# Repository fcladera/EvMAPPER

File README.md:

# EvMAPPER

This is the source code repository for EvMAPPER, a high altitude orthomapping
framework.

## Repository overview
 - `CAD`: CAD models to attach the sensor stack (EV + RGB + VN100 + range sensor) to the Falcon 4 UAV. 
 - `PCB`: PCB for time synchronization.
 - `ha_python_utils`: Python utilities for high altitude data processing.
 - `Notebooks`: Jupyter notebooks for data processing and visualization.

You can access our preprint on [arXiv](https://arxiv.org/abs/2409.18120),
and our [video presentation](https://www.youtube.com/watch?v=8mgCMnaMDdM).

## Citation
```
@article{cladera2024evmapper,
  title={EvMAPPER: High Altitude Orthomapping with Event Cameras},
  author={Cladera, Fernando and Chaney, Kenneth and Hsieh, M Ani and Taylor, Camillo J and Kumar, Vijay},
  journal={arXiv preprint arXiv:2409.18120},
  year={2024}
}
```

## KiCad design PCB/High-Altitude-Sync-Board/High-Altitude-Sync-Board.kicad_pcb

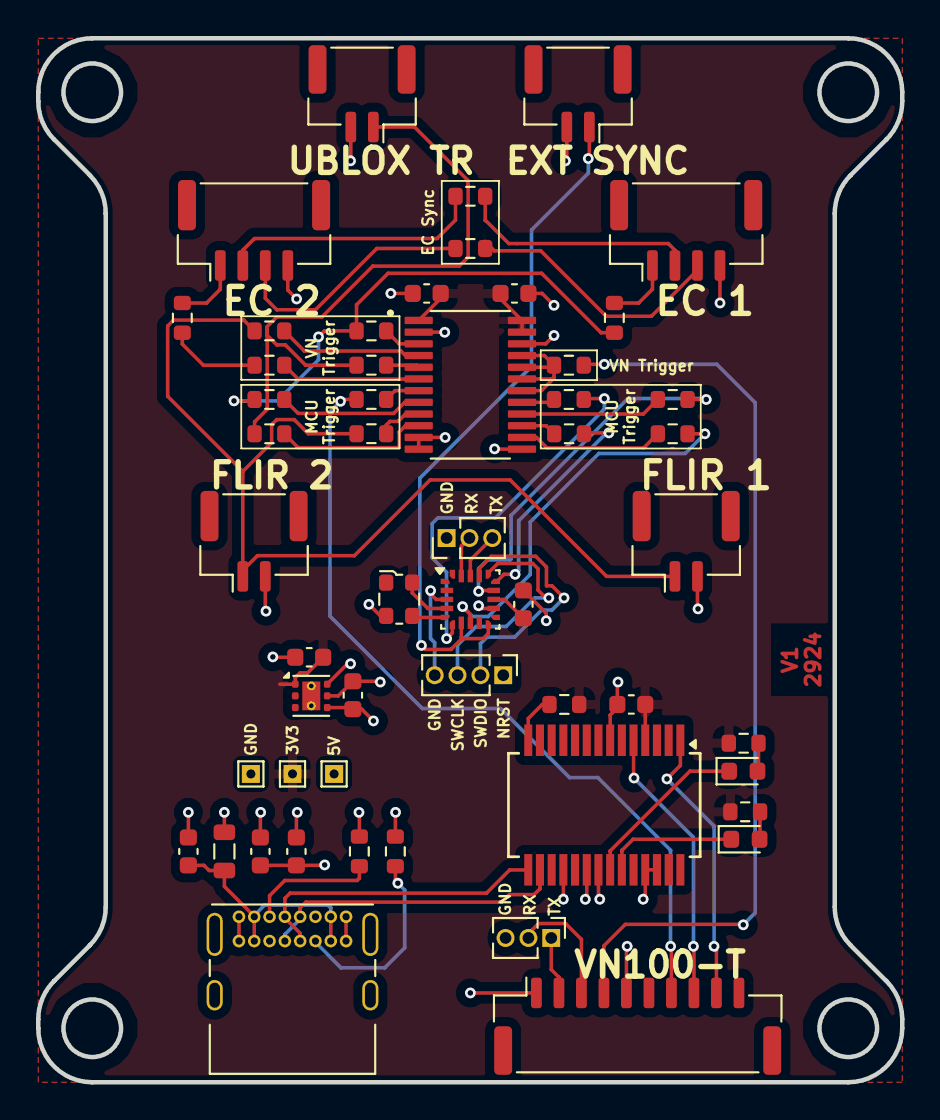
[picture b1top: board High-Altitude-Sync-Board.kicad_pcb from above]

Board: 4 copper layers, 48.0 x 58.0 mm, 53 parts (0 on the bottom side), 53 nets.

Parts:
C1, C2, C3, C5, C7: 100nF; C_0603_1608Metric
C4: 10nF_X7R; C_0603_1608Metric
C6, C9, C10: 4.7uF; C_0603_1608Metric
D1, D2: LED; LED_0603_1608Metric
J1: USB_C_Receptacle_USB2.0_14P; USB_C_Receptacle_GCT_USB4085
J2, J20: SM02B-GHS-TB; JST_GH_SM02B-GHS-TB_1x02-1MP_P1.25mm_Horizontal
J7: VN100_T_CONN; JST_GH_SM10B-GHS-TB_1x10-1MP_P1.25mm_Horizontal
J17: VN100T-UPDATE; PinHeader_1x03_P1.27mm_Vertical
J18, J19: BM02B-GHS-TBT; JST_GH_BM02B-GHS-TBT_1x02-1MP_P1.25mm_Vertical
J23, J25: BM04B-GHS-TBT; JST_GH_BM04B-GHS-TBT_1x04-1MP_P1.25mm_Vertical
J24: SWD; PinHeader_1x04_P1.27mm_Vertical
J26: UART; PinHeader_1x03_P1.27mm_Vertical
L1: MI0805K400R-10; L_0805_2012Metric
R1, R2: 5.1k; R_0603_1608Metric
R3, R4, R5, R6, R7, R8, R9, R11, R12, R13, R14, R15, R16, R19, R20, R21, R22: 0R; R_0603_1608Metric
R10, R17: 1k1; R_0603_1608Metric
R18: 10k; R_0603_1608Metric
TP1: 5V TP; TestPoint_THTPad_1.0x1.0mm_Drill0.5mm
TP2: GND TP; TestPoint_THTPad_1.0x1.0mm_Drill0.5mm
TP3: 3V3 TP; TestPoint_THTPad_1.0x1.0mm_Drill0.5mm
U1: SN74AXC8T245PWR; SOP65P640X120-24N
U2: FT232RL; SSOP-28_5.3x10.2mm_P0.65mm
U3: LP5912-3.3DRV; WSON-6-1EP_2x2mm_P0.65mm_EP1x1.6mm_ThermalVias
U4: STM32L011F3Ux; ST_UFQFPN-20_3x3mm_P0.5mm
X1: ECS-2520MV; Oscillator_SMD_ECS_2520MV-xxx-xx-4Pin_2.5x2.0mm

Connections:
+3V3: C1.1, C2.1, C3.1, C7.1, C10.1, R10.1, R17.1, R18.1, TP3.1, U1.1 (VCCA), U1.23 (VCCB), U1.24 (VCCB), U2.4 (VCCIO), U3.1 (OUT), U4.4 (VDDA), U4.13 (VDD), X1.4 (VDD)
+5V: C5.1, C6.1, C9.1, J7.1, L1.1, TP1.1, U2.20 (VCC), U3.4 (EN), U3.6 (IN)
/EC_1_TRIGGER_IN: R3.1, R11.1, R22.1
/EC_2_TRIGGER_IN: R7.1, R19.1
/EXT_SYNC: J20.1, U4.7 (PA4), U4.10 (PA7)
/FLIR_TRIGGER_IN: J18.1, J19.1, R5.1, R13.1
/HSE: U4.5 (PA0), X1.3 (OUT)
/NRST: J24.4, U4.3 (NRST)
/SWCLK: J24.2, U4.17 (PA14)
/SWDIO: J24.3, U4.16 (PA13)
/SYNC_IN_N4: J23.3, R21.2
/SYNC_IN_P3: J23.2, R20.2
/SYNC_OUT_N2: J25.3, R21.1
/SYNC_OUT_P1: J25.2, R20.1
/TIM2_CH1: R16.2, U4.8 (PA5)
/TIM2_CH2: R9.2, U4.6 (PA1)
/TIM21_CH1: R14.2, U4.15 (PA10)
/TIM21_CH2: R12.2, U4.14 (PA9)
/UBLOX_TRIGGER_IN: J2.1, R6.1, R15.1
/VN-100T-RX1: J7.3, J17.2
/VN-100T-RX2_TTL: J7.9, U2.1 (TXD)
/VN-100T-SYNC-IN: J7.7, R8.1
/VN-100T-SYNC-OUT: J7.4, R4.2
/VN-100T-TX1: J7.2, J17.1
/VN-100T-TX2_TTL: J7.8, U2.5 (RXD)
GND: C1.2, C2.2, C3.2, C4.2, C5.2, C6.2, C7.2, C9.2, C10.2, J1.A1 (GND), J1.A12 (GND), J1.B1 (GND), J1.B12 (GND), J2.2, J7.5, J17.3, J18.2, J19.2, J20.2, J23.4, J24.1, J25.4, J26.1, R1.1, R2.1, TP2.1, U1.2 (DIR1), U1.11 (DIR2), U1.12 (GND), U1.13 (GND), U1.22 (~OE), U2.7 (GND), U2.18 (GND), U2.21 (GND), U2.25 (AGND), U2.26 (TEST), U3.5 (GND), U3.7 (EP), U4.12 (VSS), X1.2 (GND)
unnamed: C4.1, J1.A4 (VBUS), J1.A9 (VBUS), J1.B4 (VBUS), J1.B9 (VBUS), L1.2
unnamed: D1.2 (A), R10.2
unnamed: D1.1 (K), U2.23 (CBUS0)
unnamed: D2.2 (A), R17.2
unnamed: D2.1 (K), U2.22 (CBUS1)
unnamed: J1.A5 (CC1), R1.2
unnamed: J1.B5 (CC2), R2.2
unnamed: J23.1, R19.2
unnamed: J25.1, R22.2
unnamed: J26.2, U4.19 (PB7)
unnamed: J26.3, U4.18 (PB6)
unnamed: R3.2, U1.3 (A1)
unnamed: R5.2, U1.4 (A2)
unnamed: R6.2, U1.5 (A3)
unnamed: R7.2, U1.6 (A4)
unnamed: R8.2, U1.7 (A5)
unnamed: R11.2, U1.8 (A6)
unnamed: R13.2, U1.9 (A7)
unnamed: R15.2, U1.10 (A8)
unnamed: R4.1, U1.18 (B4), U1.19 (B3), U1.20 (B2), U1.21 (B1)
unnamed: R9.1, U1.17 (B5)
unnamed: R12.1, U1.16 (B6)
unnamed: R14.1, U1.15 (B7)
unnamed: R16.1, U1.14 (B8)
unnamed: R18.2, U2.14 (CBUS3)
unnamed: J1.A6 (D+), J1.B6 (D+), U2.15 (USBD+)
unnamed: J1.A7 (D-), J1.B7 (D-), U2.16 (USBD-)

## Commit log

2024-07-10 First version of the hardware CAD
2024-07-12 Setup Board for PCB
2024-07-12 Removed prl file and moved PCB outline into right folder
2024-07-12 Add .gitignore for PCB dir
2024-07-15 First draft of High Altitude sync board with outline
2024-07-15 Updated .gitignore for PCB
2024-07-15 Routed RS232
2024-07-15 Routed top part of the sync board
2024-07-16 Almost final routing of High Altitude Sync Board
2024-07-17 High Altitude Sync Board - V1
2024-07-17 Updated CAD with PCB and LM5JCM lens
2024-07-17 Ignore step files and pngs in CAD
2024-07-20 Add MountingBlock to mount to Falcon 4. Fix small defects in other parts.
2024-08-01 Reduced the size of the CameraMount plate, with newer MountingBlocks
2024-08-06 Poetry pyproject.toml file
2024-08-06 Notebook to analyze IMU clock and triggers
2024-08-13 Time synchronization tests for all high frequency sensors
2024-08-20 Time synchronization notebook for all sensors
2024-08-20 Renamed time synchronization notebook
2024-08-20 Simple video generator notebook
2024-08-30 Better synchronization of all sensors. Verification notebook.
2024-09-05 Bugfix: the timestamp of the event camera changes when cutting the event stream
2024-09-05 event_extractor: simple tool to extract events to txt
2024-09-11 image_extractor notebook to get images for ODM
2024-09-26 Basic readme
